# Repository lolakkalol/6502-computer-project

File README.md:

<!-- Improved compatibility of back to top link: See: https://github.com/lolakkalol/6502-computer-project/pull/73 -->

<!--
*** Thanks for checking out the Best-README-Template. If you have a suggestion
*** that would make this better, please fork the repo and create a pull request
*** or simply open an issue with the tag "enhancement".
*** Don't forget to give the project a star!
*** Thanks again! Now go create something AMAZING! :D
-->

<!-- PROJECT SHIELDS -->
<!--
*** I'm using markdown "reference style" links for readability.
*** Reference links are enclosed in brackets [ ] instead of parentheses ( ).
*** See the bottom of this document for the declaration of the reference variables
*** for contributors-url, forks-url, etc. This is an optional, concise syntax you may use.
*** https://www.markdownguide.org/basic-syntax/#reference-style-links
-->
[![Contributors][contributors-shield]][contributors-url]
[![Forks][forks-shield]][forks-url]
[![Stargazers][stars-shield]][stars-url]
[![Issues][issues-shield]][issues-url]
<!--[![MIT License][license-shield]][license-url]
[![LinkedIn][linkedin-shield]][linkedin-url]-->

<!-- PROJECT LOGO -->
<br />
<div align="center">

  <h3 align="center">6502 Computer Project</h3>

  <p align="center">
    A 6502-based computer project!
    <br />
    <a href="https://github.com/lolakkalol/6502-computer-project"><strong>Explore the docs »</strong></a>
    <br />
    <br />
    <a href="https://github.com/lolakkalol/6502-computer-project/tree/main/programs">View Demo Programs</a>
    ·
    <a href="https://github.com/lolakkalol/6502-computer-project/issues">Report Bug</a>
    ·
    <a href="https://github.com/lolakkalol/6502-computer-project/issues">Request Feature</a>
  </p>
</div>

<!-- TABLE OF CONTENTS -->
<details>
  <summary>Table of Contents</summary>
  <ol>
    <li>
      <a href="#about-the-project">About The Project</a>
      <ul>
        <li><a href="#built-with">Built With</a></li>
      </ul>
    </li>
    <li>
      <a href="#getting-started">Getting Started</a>
      <ul>
        <li><a href="#prerequisites">Prerequisites</a></li>
        <li><a href="#installation">Installation</a></li>
      </ul>
    </li>
    <li><a href="#usage">Usage</a></li>
    <li><a href="#roadmap">Roadmap</a></li>
    <li><a href="#contributing">Contributing</a></li>
    <li><a href="#license">License</a></li>
    <li><a href="#contact">Contact</a></li>
    <li><a href="#acknowledgments">Acknowledgments</a></li>
  </ol>
</details>

<!-- ABOUT THE PROJECT -->
## About The Project

[![Product Name Screen Shot][product-screenshot]](https://example.com)

This project started thanks to [Ben Eater's](https://www.youtube.com/@BenEater) video series on his 6502-based computer, which is the basis for my project and learning experience.
The project has a very simple goal of me learning low-level embedded system development on hardware and software. To achieve this learning goal, a few project goals/milestones have been set up to steer the project in a satisfactory direction.
The computer should also not be a carbon copy of Ben Eater's computer to promote self-learning and delving into documentation and learning by doing. I believe you remember things better when you fail at something and, in the end, solve the problems that made you fail.

### Goals
These goals aim to create a 6502-based computer on a single PCB that can be expanded with modules later on.
- Learn "low-level" embedded computer architecture basics
  - Both hardware and software
- Build a 6502-based computer on a PCB which shall:
  - Be expandable, meaning you can add modules to it later (Some kind of expansion bus)
  - Output text console to a computer screen
  - Handle mouse and keyboard (USB/PS2 either or both)
  - Have serial communication capability
  - Load programs over serial into RAM (Maybe some kind of bootloader?)
  - Flash the program flash over some protocol
  - Some kind of operating system
- Try and avoid scope creep
- HAVE FUN!

<p align="right">(<a href="#readme-top">back to top</a>)</p>

### Built With
These are the currently used programs and frameworks used for building the project, for both software and hardware.

- [CA65, LD65](https://cc65.github.io/) for assembling, linking and relocating the code.
- [KiCad](https://www.kicad.org/) for designing the computer and its physical layout.
- [GNU Make](https://www.gnu.org/software/make/) for automating the build tasks of CC65 and LD65.

<p align="right">(<a href="#readme-top">back to top</a>)</p>

<!-- GETTING STARTED -->
## Getting Started

To get a local copy up and running follow these simple example steps.

### Prerequisites

* CC65 (Windows/Linux)
Download and install the cross-development package [CC65](https://github.com/cc65/cc65) (available for both Windows and Linux).

* GNU Utils (Windows)
Download `GNU make` and `CoreUtils` from https://gnuwin32.sourceforge.net/packages.html and add them to your path.

### Installation (Software)

1. Clone the repository
2. In `6502-computer-project/programs/<program name>/` simple run make
3. Flash the EEPROM using your choice of programmer

<p align="right">(<a href="#readme-top">back to top</a>)</p>

<!-- USAGE EXAMPLES -->
## Usage

This project currently has three different areas: Schematics and KiCad symbols, hardware debugger, and programs, each will be explained below.

### Schematics and KiCad symbols
Found in the folder `6502-and-friends` and `6502-schematic`, here the schematic over the computer, the custom symbols and PCB design can be found.

### Hardware debugger
Found, at the moment, in the folder `bus-sniffer`; this is simply a program for an Arduino Mega2560 sniffing and printing to the console the: Address bus, data buss and control bus.
It can also supply its own clock, which can be halted at the press of a button and send single clock pulses to support hardware debugging.

### Programs
Found in the folder `Programs`, contain all the currently constructed programs and a template for creating a new program.
Each program comes with its own make file specifying how it is to be built together with throughout commenting. 
All programs are written in 6502 assembly and most is created according to the specified template.

The template contain the following:
- `main.asm` Here is the main code.
- `lib.asm` Here, the supporting code should be put, such as sub-routines, following the example sub-routines structure.
- `start.asm` holds the start-up code and is already written in the template; it is responsible for initializing memory segments at startup.
- `makefile` Specifies how to build and link `main.asm`, `lib.asm` and `start.asm`.
- `target.cfg` Specifies the address space, segments, and their location in memory for the linker to us.

<p align="right">(<a href="#readme-top">back to top</a>)</p>

<!-- ROADMAP -->
## Roadmap
There are currently two main roadmaps, one for a Pi estimation program used to get familiar with the 6502 and another for the actual computer project.
For the Pi estimation program the computer seen in the current KiCad schematic is used.

### Pi estimation
- [ ] IEEE 754 Floating point arithmetic
  - [X] Addition/Subtraction
  - [ ] Multiplication
  - [ ] Division
  - [ ] (To be expanded upon if necessary)
- [ ] LCD printing
- [ ] Convert Floating point numbers to decimal
- [ ] Pi estimation algorithm
  - [ ] (To be expanded upon)

### 6502-based computer
- [ ] Decide desirable features
- [ ] Design schematic
  - [ ] Research chips needed
  - [ ] Plan address space
  - [ ] Create KiCad symbols for chips
  - [ ] Route connections between chips
  - [ ] (To be expanded upon)
- [ ] Operating system?

See the [open issues](https://github.com/lolakkalol/6502-computer-project/issues) for a full list of proposed features (and known issues).

<p align="right">(<a href="#readme-top">back to top</a>)</p>

## Micro documentation
Here a very small condenced documentation can be found only used as a quick reference.
The code is often commented so do not forget to look there.

### Memory map

### Floating point routines
The floating point routines are all commented on and explained in the code but have also been planned before implementation using a high-level flowchart in draw.io found below.

[Flowchart](https://drive.google.com/file/d/1zk0GJeMiMwG2__90PIV5DE1KcaoCTDiV/view?usp=sharing)

<!-- CONTRIBUTING -->
<!--## Contributing

Contributions are what make the open source community such an amazing place to learn, inspire, and create. Any contributions you make are **greatly appreciated**.

If you have a suggestion that would make this better, please fork the repo and create a pull request. You can also simply open an issue with the tag "enhancement".
Don't forget to give the project a star! Thanks again!

1. Fork the Project
2. Create your Feature Branch (`git checkout -b feature/AmazingFeature`)
3. Commit your Changes (`git commit -m 'Add some AmazingFeature'`)
4. Push to the Branch (`git push origin feature/AmazingFeature`)
5. Open a Pull Request

<p align="right">(<a href="#readme-top">back to top</a>)</p>-->

<!-- LICENSE -->
<!--## License

Distributed under the MIT License. See `LICENSE.txt` for more information.

<p align="right">(<a href="#readme-top">back to top</a>)</p>-->

<!-- CONTACT -->
## Contact

Alexander Stenlund -  alexander.stenlund@telia.com

Project Link: [https://github.com/lolakkalol/6502-computer-project](https://github.com/lolakkalol/6502-computer-project)

<p align="right">(<a href="#readme-top">back to top</a>)</p>

<!-- ACKNOWLEDGMENTS -->
## Acknowledgments

* [6502 Primer](https://wilsonminesco.com/6502primer/)
* [6502 forum](http://forum.6502.org/viewtopic.php?t=1064&start=105)
* [65SIB](http://forum.6502.org/viewtopic.php?t=1064&start=105)

<p align="right">(<a href="#readme-top">back to top</a>)</p>

<!-- MARKDOWN LINKS & IMAGES -->
<!-- https://www.markdownguide.org/basic-syntax/#reference-style-links -->
[contributors-shield]: https://img.shields.io/github/contributors/lolakkalol/6502-computer-project.svg?style=for-the-badge
[contributors-url]: https://github.com/lolakkalol/6502-computer-project/graphs/contributors
[forks-shield]: https://img.shields.io/github/forks/lolakkalol/6502-computer-project.svg?style=for-the-badge
[forks-url]: https://github.com/lolakkalol/6502-computer-project/network/members
[stars-shield]: https://img.shields.io/github/stars/lolakkalol/6502-computer-project.svg?style=for-the-badge
[stars-url]: https://github.com/lolakkalol/6502-computer-project/stargazers
[issues-shield]: https://img.shields.io/github/issues/lolakkalol/6502-computer-project.svg?style=for-the-badge
[issues-url]: https://github.com/lolakkalol/6502-computer-project/issues
[license-shield]: https://img.shields.io/github/license/lolakkalol/6502-computer-project.svg?style=for-the-badge
[license-url]: https://github.com/lolakkalol/6502-computer-project/blob/master/LICENSE.txt
[linkedin-shield]: https://img.shields.io/badge/-LinkedIn-black.svg?style=for-the-badge&logo=linkedin&colorB=555
[linkedin-url]: https://linkedin.com/in/othneildrew
[product-screenshot]: images/screenshot.png

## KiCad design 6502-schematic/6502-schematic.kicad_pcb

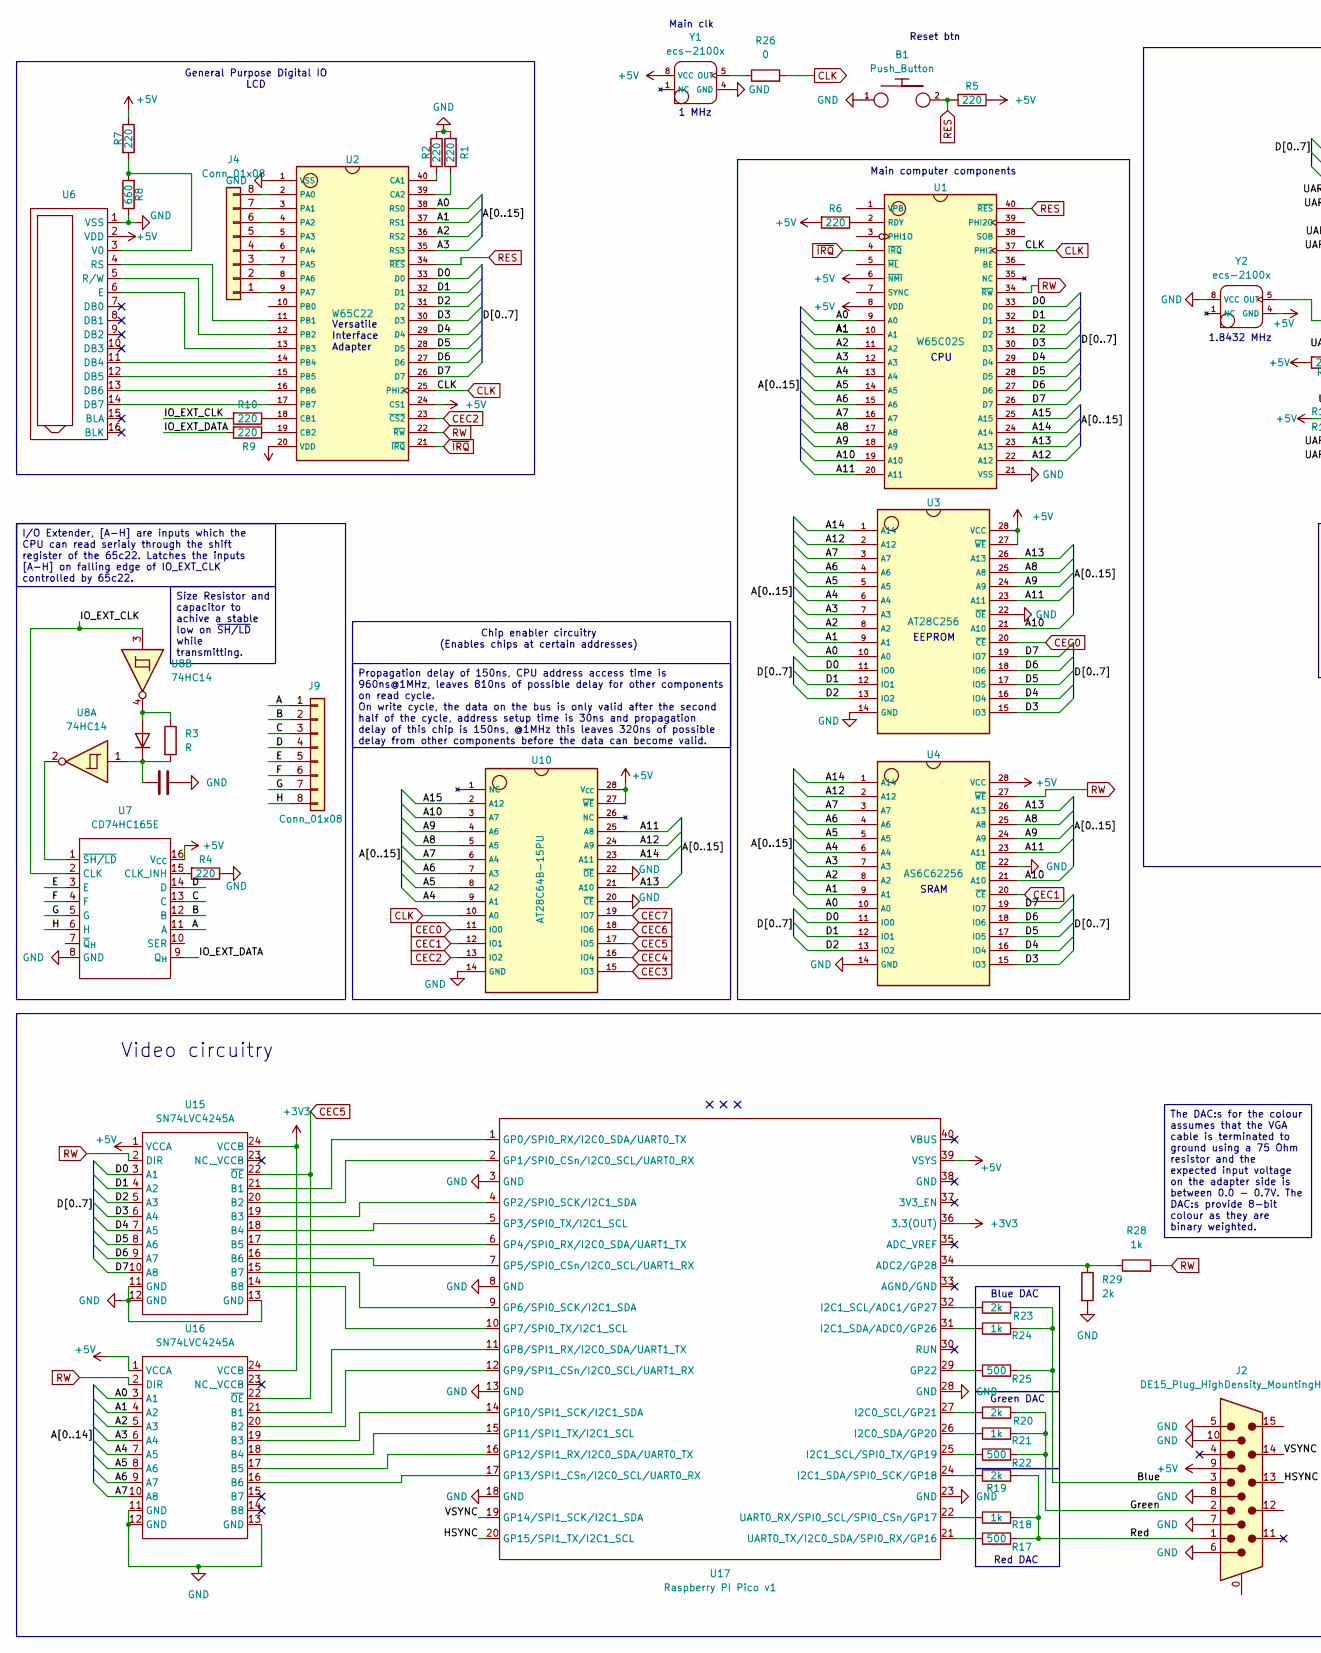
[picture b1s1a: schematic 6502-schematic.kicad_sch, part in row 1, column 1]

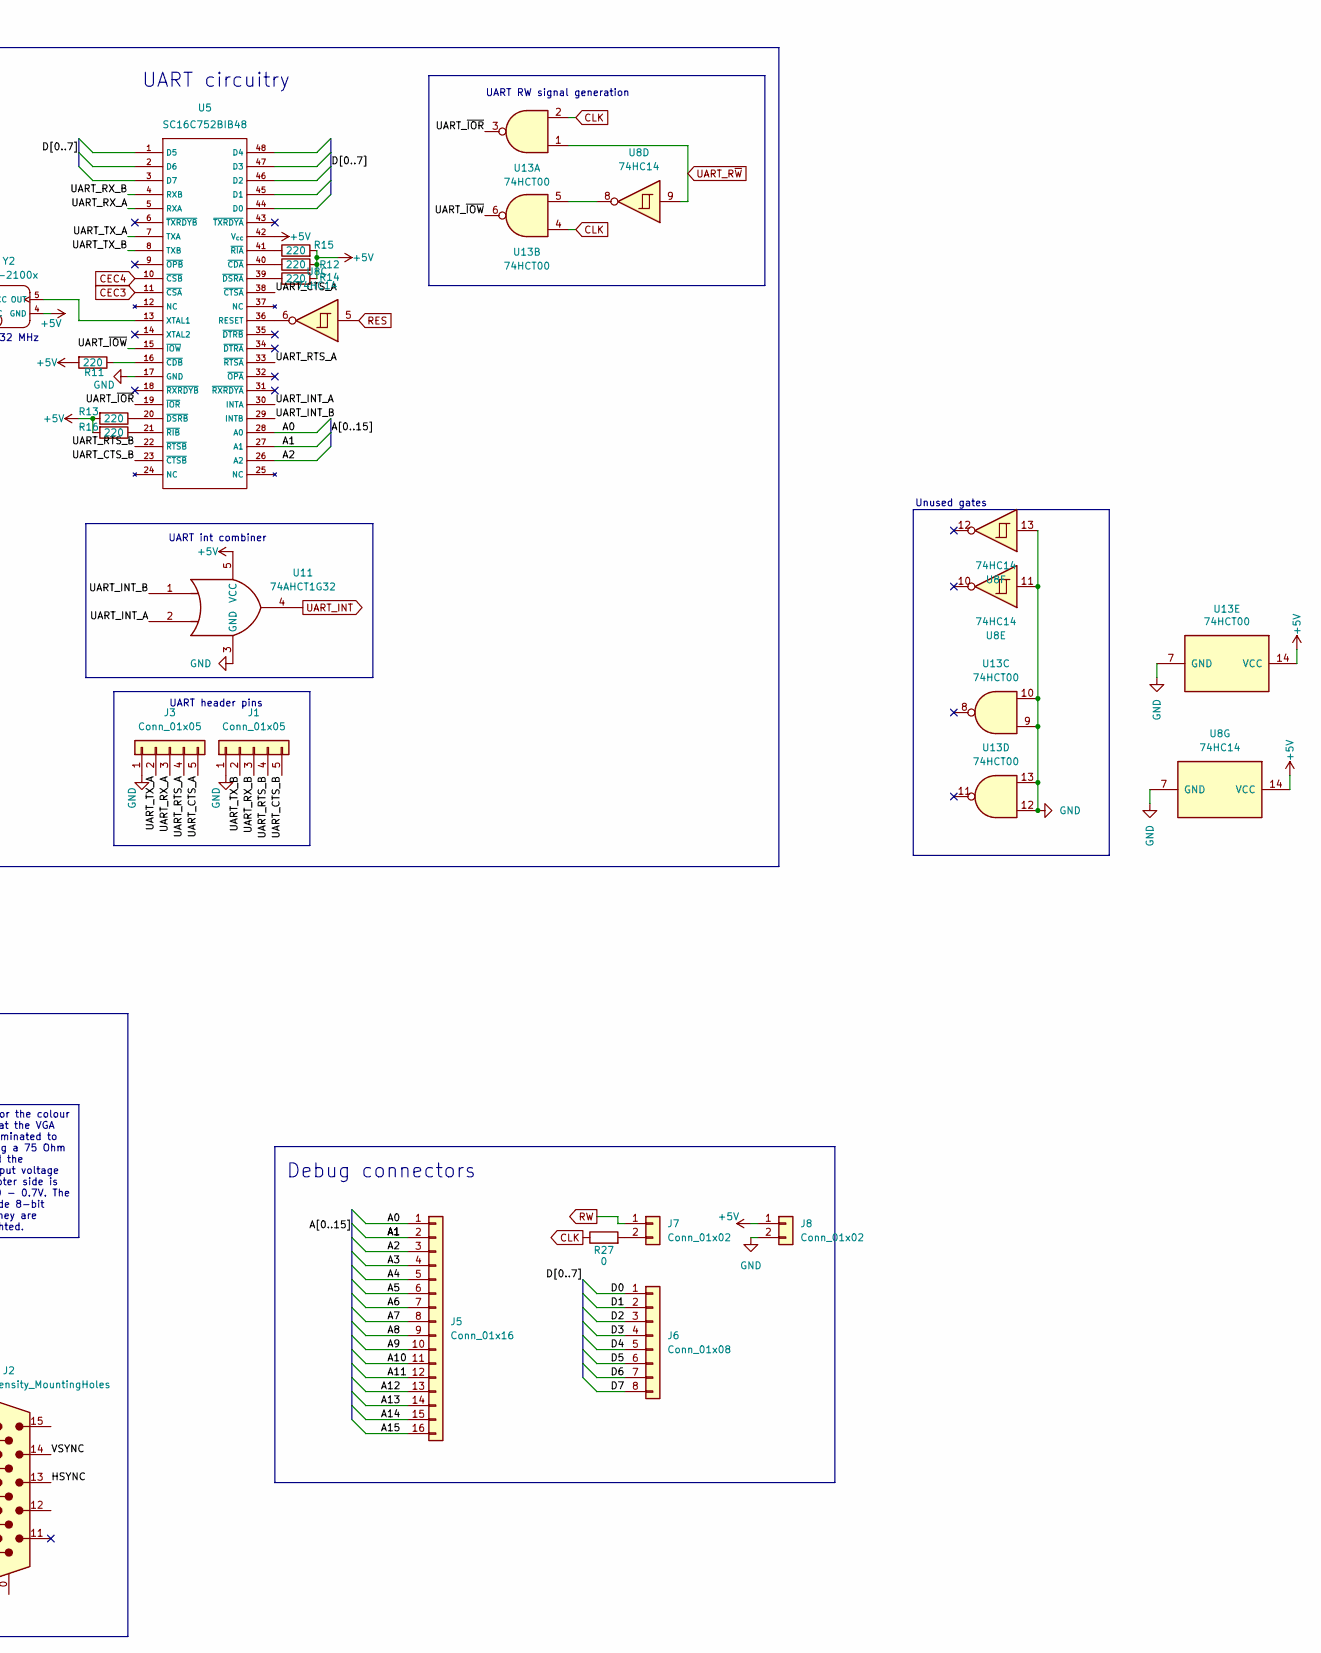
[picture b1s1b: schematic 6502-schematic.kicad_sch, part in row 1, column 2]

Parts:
B1: Push_Button; KSA_Tactile_SPST
C1: C; C_Disc_D9.0mm_W5.0mm_P10.00mm
D1: D; D_5W_P10.16mm_Horizontal
J1, J3: Conn_01x05; PinHeader_1x05_P2.54mm_Vertical
J2: DE15_Plug_HighDensity_MountingHoles; PinHeader_2x08_P2.54mm_Vertical
J4, J6, J9: Conn_01x08; PinHeader_1x08_P2.54mm_Vertical
J5: Conn_01x16; PinHeader_1x16_P2.54mm_Vertical
J7, J8: Conn_01x02; PinHeader_1x02_P2.54mm_Vertical
R1, R2, R4, R5, R6, R7, R9, R10, R11, R12, R13, R14, R15, R16: 220; R_Axial_DIN0204_L3.6mm_D1.6mm_P2.54mm_Vertical
R3: R; R_Axial_DIN0204_L3.6mm_D1.6mm_P2.54mm_Vertical
R8: 660; R_Axial_DIN0204_L3.6mm_D1.6mm_P2.54mm_Vertical
R17, R22, R25: 500; R_Axial_DIN0204_L3.6mm_D1.6mm_P2.54mm_Vertical
R18, R21, R24, R28: 1k; R_Axial_DIN0204_L3.6mm_D1.6mm_P2.54mm_Vertical
R19, R20, R23, R29: 2k; R_Axial_DIN0204_L3.6mm_D1.6mm_P2.54mm_Vertical
R26, R27: 0; R_0805_2012Metric_Pad1.20x1.40mm_HandSolder
U1: W65C02S; DIP-40_W15.24mm_LongPads
U2: W65C22; DIP-40_W15.24mm_LongPads
U3: AT28C256; DIP-28_W15.24mm_LongPads
U4: AS6C62256; DIP-28_W15.24mm_LongPads
U5: SC16C752BIB48; LQFP-48_7x7mm_P0.5mm
U6: PinHeader_1x16_P2.54mm_Vertical
U7: CD74HC165E; DIP-16_W7.62mm_LongPads
U8: 74HC14; CERDIP-14_W7.62mm_SideBrazed_LongPads
U10: AT28C64B-15PU; DIP-28_W15.24mm_LongPads
U11: 74AHCT1G32; SOT-23-5_HandSoldering
U13: 74HCT00; DIP-14_W7.62mm_LongPads
U15, U16: SN74LVC4245A; SOIC-24W_7.5x15.4mm_P1.27mm
U17: Raspberry PI Pico v1; Raspberry_PI_Pico_Socket
Y1, Y2: ecs-2100x; ECS-2100X

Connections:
+3V3: U15.24 (VCCB), U16.24 (VCCB), U17.36 (3.3(OUT))
+5V: J2.9, J8.1, R5.1, R6.2, R7.1, R11.2, R12.2, R13.2, R14.2, R15.2, R16.2, U1.6 (~NMI), U1.8 (VDD), U2.20 (VDD), U2.24 (CS1), U3.27 (~WE), U3.28 (VCC), U4.28 (VCC), U5.42 (V_{cc}), U6.2 (VDD), U7.16 (V_{CC}), U8.14 (VCC), U10.27 (~WE), U10.28 (V_{CC}), U11.5 (VCC), U13.14 (VCC), U15.1 (VCCA), U16.1 (VCCA), U17.39 (VSYS), Y1.8 (VCC), Y2.4 (GND)
/A: J9.1, U7.11 (A)
/A0: J5.1, U1.9 (A0), U2.38 (RS0), U3.10 (A0), U4.10 (A0), U5.28 (A0), U16.3 (A1)
/A1: J5.2, U1.10 (A1), U2.37 (RS1), U3.9 (A1), U4.9 (A1), U5.27 (A1), U16.4 (A2)
/A2: J5.3, U1.11 (A2), U2.36 (RS2), U3.8 (A2), U4.8 (A2), U5.26 (A2), U16.5 (A3)
/A3: J5.4, U1.12 (A3), U2.35 (RS3), U3.7 (A3), U4.7 (A3), U16.6 (A4)
/A4: J5.5, U1.13 (A4), U3.6 (A4), U4.6 (A4), U10.9 (A1), U16.7 (A5)
/A5: J5.6, U1.14 (A5), U3.5 (A5), U4.5 (A5), U10.8 (A2), U16.8 (A6)
/A6: J5.7, U1.15 (A6), U3.4 (A6), U4.4 (A6), U10.7 (A3), U16.9 (A7)
/A7: J5.8, U1.16 (A7), U3.3 (A7), U4.3 (A7), U10.6 (A4), U16.10 (A8)
/A8: J5.9, U1.17 (A8), U3.25 (A8), U4.25 (A8), U10.5 (A5)
/A9: J5.10, U1.18 (A9), U3.24 (A9), U4.24 (A9), U10.4 (A6)
/A10: J5.11, U1.19 (A10), U3.21 (A10), U4.21 (A10), U10.3 (A7)
/A11: J5.12, U1.20 (A11), U3.23 (A11), U4.23 (A11), U10.25 (A8)
/A12: J5.13, U1.22 (A12), U3.2 (A12), U4.2 (A12), U10.24 (A9)
/A13: J5.14, U1.23 (A13), U3.26 (A13), U4.26 (A13), U10.21 (A10)
/A14: J5.15, U1.24 (A14), U3.1 (A14), U4.1 (A14), U10.23 (A11)
/A15: J5.16, U1.25 (A15), U10.2 (A12)
/B: J9.2, U7.12 (B)
/Blue: J2.3, R23.2, R24.2, R25.2
/C: J9.3, U7.13 (C)
/D: J9.4, U7.14 (D)
/D0: J6.1, U1.33 (D0), U2.33 (D0), U3.11 (IO0), U4.11 (IO0), U15.3 (A1)
/D1: J6.2, U1.32 (D1), U2.32 (D1), U3.12 (IO1), U4.12 (IO1), U15.4 (A2)
/D2: J6.3, U1.31 (D2), U2.31 (D2), U3.13 (IO2), U4.13 (IO2), U15.5 (A3)
/D3: J6.4, U1.30 (D3), U2.30 (D3), U3.15 (IO3), U4.15 (IO3), U15.6 (A4)
/D4: J6.5, U1.29 (D4), U2.29 (D4), U3.16 (IO4), U4.16 (IO4), U15.7 (A5)
/D5: J6.6, U1.28 (D5), U2.28 (D5), U3.17 (IO5), U4.17 (IO5), U15.8 (A6)
/D6: J6.7, U1.27 (D6), U2.27 (D6), U3.18 (IO6), U4.18 (IO6), U15.9 (A7)
/D7: J6.8, U1.26 (D7), U2.26 (D7), U3.19 (IO7), U4.19 (IO7), U15.10 (A8)
/E: J9.5, U7.3 (E)
/F: J9.6, U7.4 (F)
/G: J9.7, U7.5 (G)
/Green: J2.2, R20.2, R21.2, R22.2
/H: J9.8, U7.6 (H)
/HSYNC: J2.13, U17.20 (GP15/SPI1_TX/I2C1_SCL)
/IO_EXT_CLK: R10.2, U7.2 (CLK), U8.3
/IO_EXT_DATA: R9.2, U7.9 (Q_{H})
/Red: J2.1, R17.2, R18.2, R19.2
/UART_CTS_A: J3.5, U5.38 (~CTSA)
/UART_CTS_B: J1.5, U5.23 (~CTSB)
/UART_INT_A: U5.30 (INTA), U11.2
/UART_INT_B: U5.29 (INTB), U11.1
/UART_RTS_A: J3.4, U5.33 (~RTSA)
/UART_RTS_B: J1.4, U5.22 (~RTSB)
/UART_RX_A: J3.3, U5.5 (RXA)
/UART_RX_B: J1.3, U5.4 (RXB)
/UART_TX_A: J3.2, U5.7 (TXA)
/UART_TX_B: J1.2, U5.8 (TXB)
/UART_~IOR: U5.19 (~IOR), U13.3
/UART_~IOW: U5.15 (~IOW), U13.6
/VSYNC: J2.14, U17.19 (GP14/SPI1_SCK/I2C1_SDA)
CEC0: U3.20 (~CE), U10.11 (IO0)
CEC1: U4.20 (~CE), U10.12 (IO1)
CEC2: U2.23 (~CS2), U10.13 (IO2)
CEC3: U5.11 (~CSA), U10.15 (IO3)
CEC4: U5.10 (~CSB), U10.16 (IO4)
CEC5: U10.17 (IO5), U15.22 (~OE), U16.22 (~OE)
CEC6: U10.18 (IO6)
CEC7: U10.19 (IO7)
CLK: R26.2, R27.1, U1.37 (PHI2), U2.25 (PHI2), U10.10 (A0), U13.2, U13.4
GND: B1.1, C1.2, J1.1, J2.5, J2.6, J2.7, J2.8, J2.10, J3.1, J8.2, R1.2, R2.1, R4.1, R8.1, R29.2, U1.21 (VSS), U2.1 (VSS), U3.14 (GND), U3.22 (~OE), U4.14 (GND), U4.22 (~OE), U5.17 (GND), U6.1 (VSS), U7.8 (GND), U8.7 (GND), U8.11, U8.13, U10.14 (GND), U10.20 (~CE), U10.22 (~OE), U11.3 (GND), U13.7 (GND), U13.9, U13.10, U13.12, U13.13, U15.11 (GND), U15.12 (GND), U15.13 (GND), U16.11 (GND), U16.12 (GND), U16.13 (GND), U17.3 (GND), U17.8 (GND), U17.13 (GND), U17.18 (GND), U17.23 (GND), U17.28 (GND), Y1.4 (GND), Y2.8 (VCC)
unnamed: D1.2 (A), R3.1, U8.4
unnamed: C1.1, D1.1 (K), R3.2, U8.1
unnamed: J4.1, U2.9 (PA7)
unnamed: J4.2, U2.8 (PA6)
unnamed: J4.3, U2.7 (PA5)
unnamed: J4.4, U2.6 (PA4)
unnamed: J4.5, U2.5 (PA3)
unnamed: J4.6, U2.4 (PA2)
unnamed: J4.7, U2.3 (PA1)
unnamed: J4.8, U2.2 (PA0)
unnamed: J7.2, R27.2
unnamed: R6.1, U1.2 (RDY)
unnamed: R2.2, U2.40 (CA1)
unnamed: R1.1, U2.39 (CA2)
unnamed: R10.1, U2.18 (CB1)
unnamed: R9.1, U2.19 (CB2)
unnamed: U2.11 (PB1), U6.4 (RS)
unnamed: U2.12 (PB2), U6.5 (R/W)
unnamed: U2.13 (PB3), U6.6 (E)
unnamed: U2.14 (PB4), U6.11 (DB4)
unnamed: U2.15 (PB5), U6.12 (DB5)
unnamed: U2.16 (PB6), U6.13 (DB6)
unnamed: U2.17 (PB7), U6.14 (DB7)
unnamed: U5.36 (RESET), U8.6
unnamed: U5.13 (XTAL1), Y2.5 (OUT)
unnamed: R12.1, U5.40 (~CDA)
unnamed: R11.1, U5.16 (~CDB)
unnamed: R14.1, U5.39 (~DSRA)
unnamed: R13.1, U5.20 (~DSRB)
unnamed: R15.1, U5.41 (~RIA)
unnamed: R16.1, U5.21 (~RIB)
unnamed: R7.2, R8.2, U6.3 (V0)
unnamed: R4.2, U7.15 (CLK_INH)
unnamed: U7.1 (~SH/LD), U8.2
unnamed: U8.8, U13.5
unnamed: U15.21 (B1), U17.1 (GP0/SPI0_RX/I2C0_SDA/UART0_TX)
unnamed: U15.20 (B2), U17.2 (GP1/SPI0_CSn/I2C0_SCL/UART0_RX)
unnamed: U15.19 (B3), U17.4 (GP2/SPI0_SCK/I2C1_SDA)
unnamed: U15.18 (B4), U17.5 (GP3/SPI0_TX/I2C1_SCL)
unnamed: U15.17 (B5), U17.6 (GP4/SPI0_RX/I2C0_SDA/UART1_TX)
unnamed: U15.16 (B6), U17.7 (GP5/SPI0_CSn/I2C0_SCL/UART1_RX)
unnamed: U15.15 (B7), U17.9 (GP6/SPI0_SCK/I2C1_SDA)
unnamed: U15.14 (B8), U17.10 (GP7/SPI0_TX/I2C1_SCL)
unnamed: U16.21 (B1), U17.11 (GP8/SPI1_RX/I2C0_SDA/UART1_TX)
unnamed: U16.20 (B2), U17.12 (GP9/SPI1_CSn/I2C0_SCL/UART1_RX)
unnamed: U16.19 (B3), U17.14 (GP10/SPI1_SCK/I2C1_SDA)
unnamed: U16.18 (B4), U17.15 (GP11/SPI1_TX/I2C1_SCL)
unnamed: U16.17 (B5), U17.16 (GP12/SPI1_RX/I2C0_SDA/UART0_TX)
unnamed: U16.16 (B6), U17.17 (GP13/SPI1_CSn/I2C0_SCL/UART0_RX)
unnamed: R28.1, R29.1, U17.34 (ADC2/GP28)
unnamed: R25.1, U17.29 (GP22)
unnamed: R20.1, U17.27 (I2C0_SCL/GP21)
unnamed: R21.1, U17.26 (I2C0_SDA/GP20)
unnamed: R23.1, U17.32 (I2C1_SCL/ADC1/GP27)
unnamed: R22.1, U17.25 (I2C1_SCL/SPI0_TX/GP19)
unnamed: R24.1, U17.31 (I2C1_SDA/ADC0/GP26)
unnamed: R19.1, U17.24 (I2C1_SDA/SPI0_SCK/GP18)
unnamed: R18.1, U17.22 (UART0_RX/SPI0_SCL/SPI0_CSn/GP17)
unnamed: R17.1, U17.21 (UART0_TX/I2C0_SDA/SPI0_RX/GP16)
unnamed: R26.1, Y1.5 (OUT)
RES: B1.2, R5.2, U1.40 (~RES), U2.34 (~RES), U8.5
RW: J7.1, R28.2, U1.34 (~RW), U2.22 (~RW), U4.27 (~WE), U15.2 (DIR), U16.2 (DIR)
UART_INT: U11.4
UART_R~W: U8.9, U13.1
~IRQ: U1.4 (~IRQ), U2.21 (~IRQ)

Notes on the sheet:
UART int combiner
Blue DAC
Chip enabler circuitry (Enables chips at certain addresses)
Red DAC
Green DAC
UART circuitry
UART header pins
Unused gates
1 MHz
Reset btn
Versatile Interface Adapter
CPU
Main clk
Main computer components
1.8432 MHz
SRAM
UART RW signal generation
General Purpose Digital IO LCD
Debug connectors
Video circuitry
EEPROM
I/O Extender, [A-H] are inputs which the CPU can read serialy through the shift register of the 65c22. Latches the inputs [A-H] on falling edge of IO_EXT_CLK controlled by 65c22.
Size Resistor and capacitor to achive a stable low on ~{SH/LD} while transmitting.
Propagation delay of 150ns, CPU address access time is 960ns@1MHz, leaves 810ns of possible delay for other components on read cycle. On write cycle, the data on the bus is only valid after the second half of the cycle, address setup time is 30ns and propagation delay of this chip is 150ns, @1MHz t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
The DAC:s for the colour assumes that the VGA cable is terminated to ground using a 75 Ohm resistor and the expected input voltage on the adapter side is between 0.0 - 0.7V. The DAC:s provide 8-bit colour as they are binary weighted.

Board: 2 copper layers, 57 parts (0 on the bottom side), 125 nets, no tracks yet.

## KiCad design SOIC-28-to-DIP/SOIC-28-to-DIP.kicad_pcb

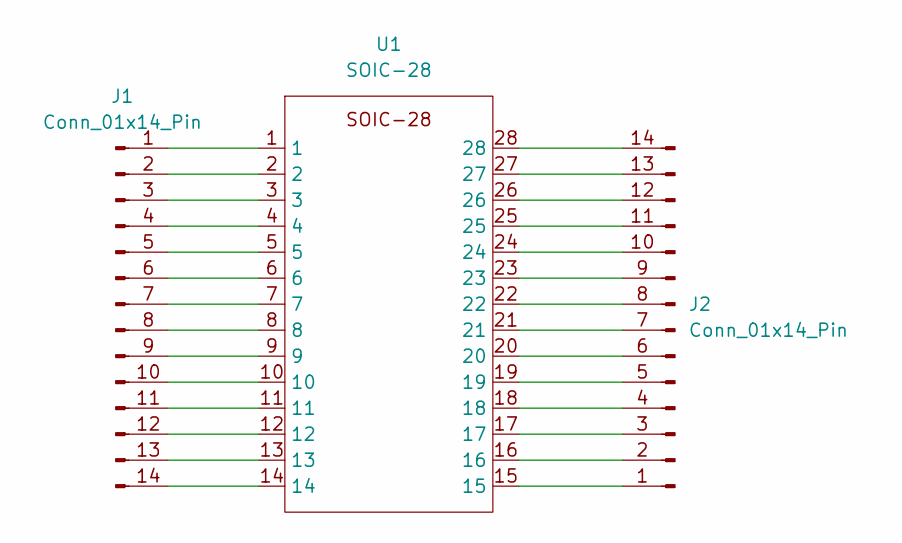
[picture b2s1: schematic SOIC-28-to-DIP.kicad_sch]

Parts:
J1, J2: Conn_01x14_Pin; PinHeader_1x14_P2.54mm_Vertical
U1: SOIC-28; SOIC-28W_7.5x18.7mm_P1.27mm

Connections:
unnamed: J1.1, U1.1
unnamed: J1.2, U1.2
unnamed: J1.3, U1.3
unnamed: J1.4, U1.4
unnamed: J1.5, U1.5
unnamed: J1.6, U1.6
unnamed: J1.7, U1.7
unnamed: J1.8, U1.8
unnamed: J1.9, U1.9
unnamed: J1.10, U1.10
unnamed: J1.11, U1.11
unnamed: J1.12, U1.12
unnamed: J1.13, U1.13
unnamed: J1.14, U1.14
unnamed: J2.1, U1.15
unnamed: J2.2, U1.16
unnamed: J2.3, U1.17
unnamed: J2.4, U1.18
unnamed: J2.5, U1.19
unnamed: J2.6, U1.20
unnamed: J2.7, U1.21
unnamed: J2.8, U1.22
unnamed: J2.9, U1.23
unnamed: J2.10, U1.24
unnamed: J2.11, U1.25
unnamed: J2.12, U1.26
unnamed: J2.13, U1.27
unnamed: J2.14, U1.28

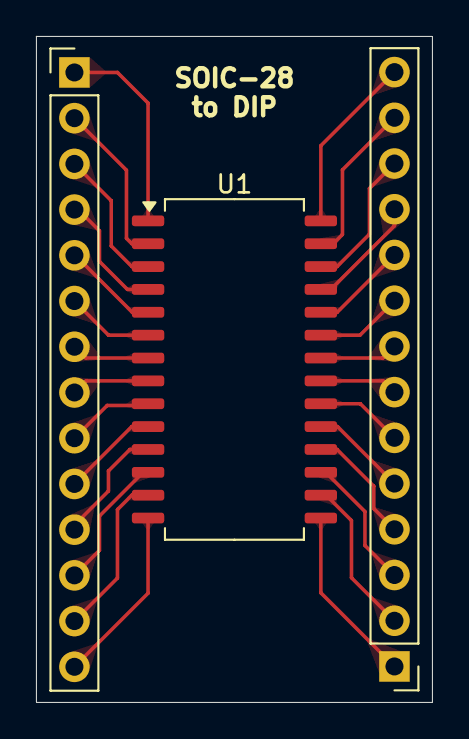
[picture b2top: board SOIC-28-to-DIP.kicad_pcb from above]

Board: 2 copper layers, 22.0 x 37.0 mm, 3 parts (0 on the bottom side), 28 nets.

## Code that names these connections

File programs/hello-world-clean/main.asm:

; Author: Alexander Stenlund
; Description: Writes the text "Hello, world!" to an LCD screen. It does this 
; though a memory mapped 65c22 VIA using both ports A and B. The LCD is 
; initilised to 8 bit mode and communicated with in a parallell bus on 
; port A and B.

.segment "CODE"

; Text to write to LCD
strHello: .asciiz "Hello, world!"
lenHello: .byte .STRLEN("Hello, world!")

; VIA Register addresses
;DDRA = $6003
DDRB = $6002
;IORA = $6001
IORB = $6000

; *************************
; *   SET UP 4-bit mode   *
; *************************
start:
JSR setup_up_LCD


; *******************
; * Write to screen *
; *******************

; Loop index
LDX #0

; 1  2  4  8 10  20  40  80
; NC RS RW E PB4 PB5 PB6 PB7

; Write string strHello to screen
writeLoop:
    ; Send first half of command (Upper char bytes)
    LDA strHello, X ; Load the character at address acc + X
    AND #$F0 ; Set all lower bits to zero
    ORA #$02 ; Set RS pin
    JSR command_LCD

    ; Send first half of command (Lower char bytes)
    LDA strHello, X ; Load the character at address acc + X
    ASL ; Shift the lower 4 bits up to the higher 4
    ASL
    ASL
    ASL
    ORA #$02 ; Set RS pin
    JSR command_LCD

    INX
    CPX lenHello
    BNE writeLoop

inf_loop: JMP inf_loop ; If at end we loop

; *******************
; *   Sub-routines  *
; *******************

setup_up_LCD:
; Set DDRB to output
LDA #$FF
STA DDRB

; Function set
LDA #$20 ; pin PB5
JSR command_LCD

; Function set
JSR command_LCD ; Repeat previous
JSR command_LCD ; Repeat previous

; Display on/off control
LDA #$00
JSR command_LCD

LDA #$E0 ; pins PB5 PB6 PB7
JSR command_LCD

; Entry mode set
LDA #$00
JSR command_LCD

LDA #$60 ; pins PB5 PB6
JSR command_LCD

RTS

; This sub-routine sends whatever data is in the 
; accumalator to the LCD.
command_LCD:
PHA

STA IORB ; Might be able to remove this instruction, test!
ORA #$08 ; pin E
STA IORB
LDA #$00 ; Setting all data to 0 should be fine...
STA IORB

PLA

JSR delay

RTS

delay:
PHA ; Save the acumalator
TXA ; Save index X in acumalator

LDX #$FF      ; 2
    loop:
    DEX       ; 2
    CPX #$0   ; 2
    BNE loop  ; 2

TAX ; Transer index X from acumalator
PLA ; Pull acumalator from stack
RTS

; 1  2  4  8 10  20  40  80
; NC RS RW E PB4 PB5 PB6 PB7

; Sets 6502 zeroflag if the busy flag from the LCD is set
; Not working :(
get_LCD_BF:

; Set data pins to inputs zero their register
LDA #$0F
STA DDRB
LDA #$4 ; Set pin RW

; Read busy flag
LDA IORB ; Will also get that pin RW is SET!!
AND #$80 ; PB7
CMP #$80 

; Set zero flag if BF set


; Set data on bus to zero

; Change PB4-7 to output

RTS

.segment "PC_START"
.WORD start

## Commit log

2023-12-18 Added objects and compiler program to be ignored
2023-12-18 Updated layout
2023-12-18 Removed unused filed
2023-12-18 Updated bus-sniffer
2023-12-18 Added two hello world programs, one clean with loop and one less clean with everything being sequential
2023-12-18 Added KiCad lock files to be ignored
2023-12-20 Changed LCD interface and code to 4-bit mode
2023-12-21 Moved LCD initilization to subreoutine
2023-12-21 Added project template for easier starting projects
2023-12-22 Expanded the template project to include the segments: DATA, BSS and LOAD. Seperated the reset vector calculation into a seperate .asm file
2023-12-22 Added comment structure to use
2023-12-22 Added loading routine for the DATA section in the LOAD section
2023-12-22 Added RODATA section
2023-12-26 First attempt at 32 bit floting point arithmetic
2023-12-27 Added logic to give the absolute value of the two's complement when result is negative, and normalization (leading one)
2023-12-30 Fixed run time page boundry safety check in loading DATA and ZP into RAM
2023-12-30 Added exception flags for IEEE754 into ZP
2024-01-01 Added roundTiesToEven and extra float explanation
2024-01-01 Removed no longer compatible sub-routines
2024-01-12 Finished floating point add/sub routine (untested)
2024-01-13 Extended a branch instruction to jump more than 127 bytes. Fixed Negate two's complement to do so correctly
2024-01-13 Fixed Is exponent 1? to actualy compare against 1 instead of 0
2024-01-13 Added a jump to when result was zero to skip handling of sub-normal numbers
2024-01-14 Added UNPACK32_TO_FLOAT_A and UNPACK32_TO_FLOAT_B
2025-08-16 A lot of changes...
    Re drew the schematic, now contains an extra EEPROM which handles address glue logic.
    arduino debugger now decodes instructions on the databus
    Some new scripts which generate the address map for the new EEPROM gluelogic
2025-08-16 Finished schematic
    Finished wiring up Raspberry pico up to the databus
    Added debug connectors
    set the footprint of all symbols
    Started with layout
